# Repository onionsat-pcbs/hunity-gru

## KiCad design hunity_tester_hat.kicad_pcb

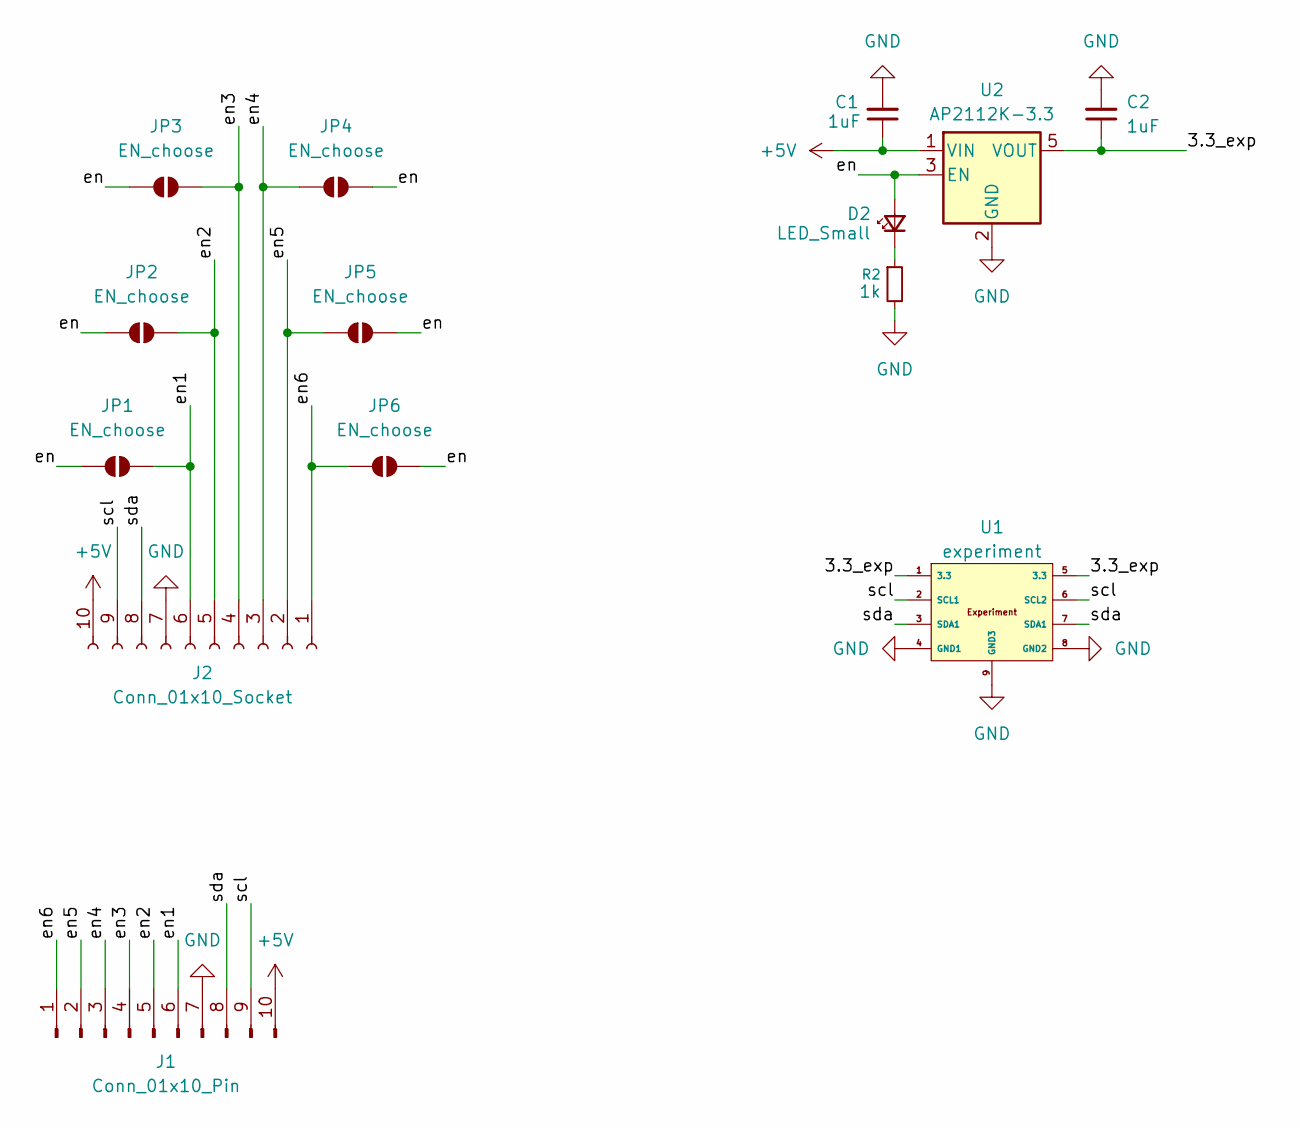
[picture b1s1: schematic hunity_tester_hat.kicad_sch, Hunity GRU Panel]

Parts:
C1, C2: 1uF; C_0603_1608Metric
D2: LED_Small; LED_0603_1608Metric
J1: Conn_01x10_Pin; PinHeader_1x10_P2.54mm_Horizontal
J2: Conn_01x10_Socket; PinSocket_1x10_P2.54mm_Horizontal
JP1, JP2, JP3, JP4, JP5, JP6: EN_choose; solder_jumper
R2: 1k; R_0603_1608Metric
U1: experiment; experiment_footprint
U2: AP2112K-3.3; SOT-23-5

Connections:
+5V: C1.1, J1.10, J2.10, U2.1 (VIN)
/3.3_exp: C2.1, U1.1 (3.3), U1.5 (3.3), U2.5 (VOUT)
/en: D2.2 (A), JP1.1 (A), JP2.1 (A), JP3.1 (A), JP4.2 (B), JP5.2 (B), JP6.2 (B), U2.3 (EN)
/en1: J1.6, J2.6, JP1.2 (B)
/en2: J1.5, J2.5, JP2.2 (B)
/en3: J1.4, J2.4, JP3.2 (B)
/en4: J1.3, J2.3, JP4.1 (A)
/en5: J1.2, J2.2, JP5.1 (A)
/en6: J1.1, J2.1, JP6.1 (A)
/scl: J1.9, J2.9, U1.2 (SCL1), U1.6 (SCL2)
/sda: J1.8, J2.8, U1.3 (SDA1), U1.7 (SDA1)
GND: C1.2, C2.2, J1.7, J2.7, R2.2, U1.4 (GND1), U1.8 (GND2), U1.9 (GND3), U2.2 (GND)
unnamed: D2.1 (K), R2.1

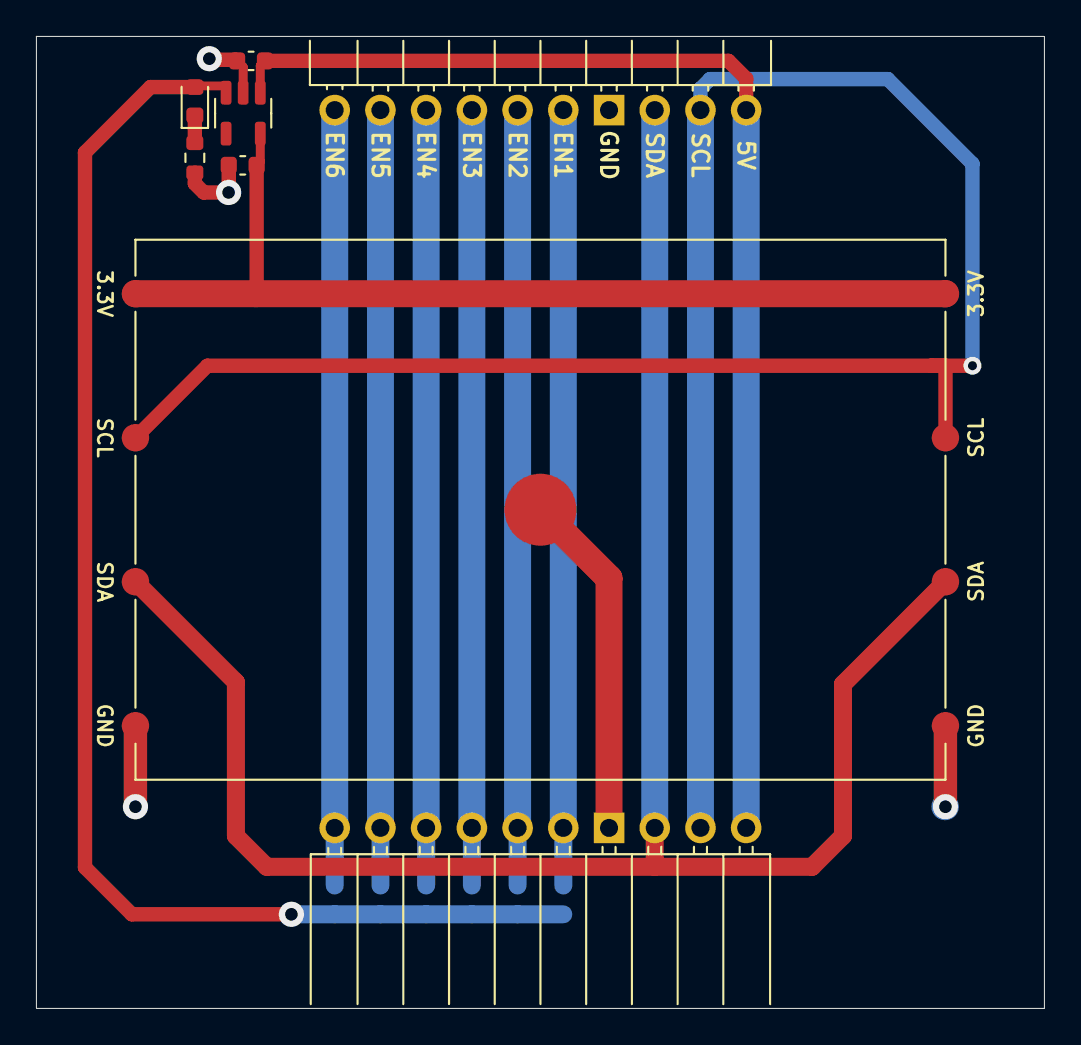
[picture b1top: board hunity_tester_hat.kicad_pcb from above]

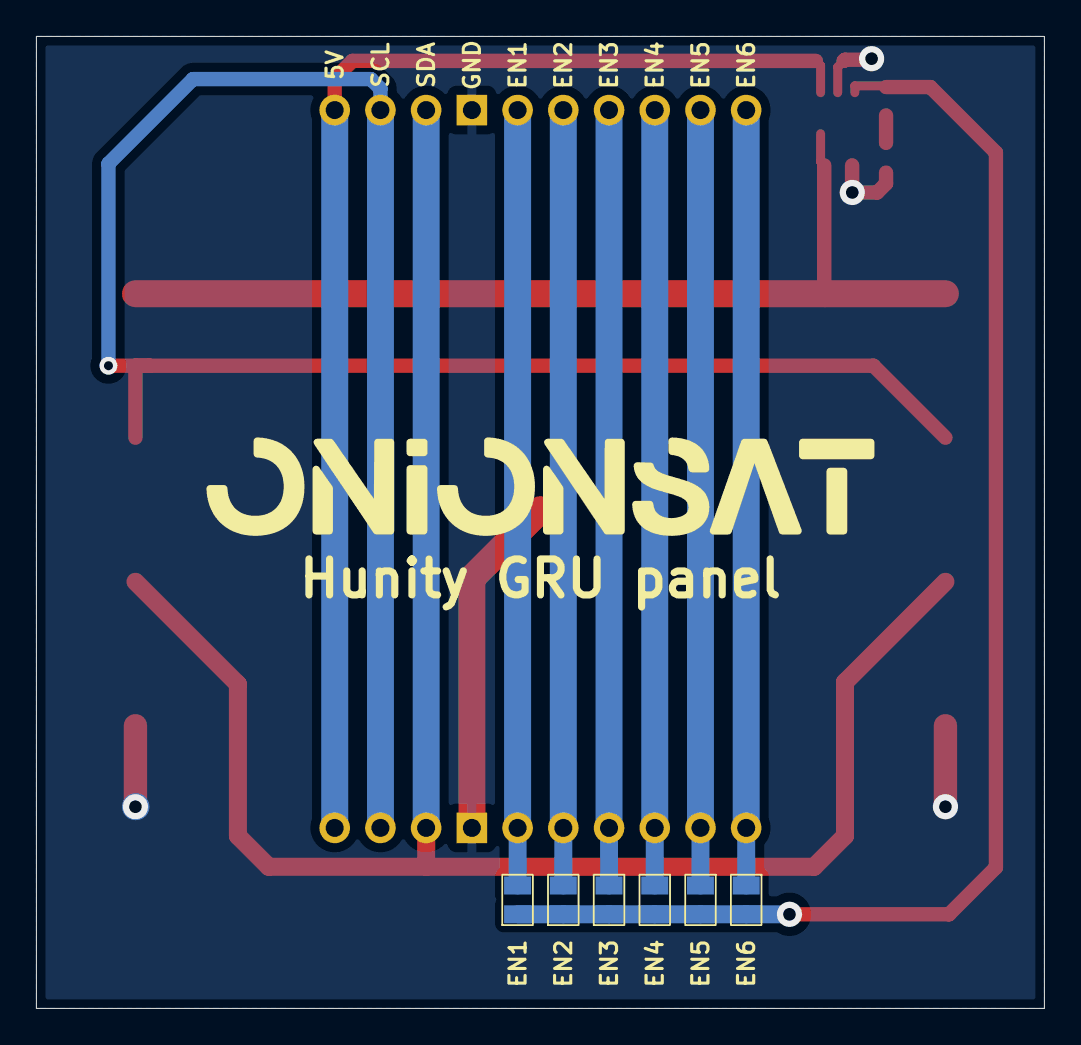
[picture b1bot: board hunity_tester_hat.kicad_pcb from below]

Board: 2 copper layers, 56.0 x 54.0 mm, 14 parts (6 on the bottom side), 13 nets.

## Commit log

2025-05-28 initial relase
2025-05-29 matrica nyákra (62x15mm)
2025-05-29 last fixes
2025-05-29 generating production files + labeling + DRC
2025-05-29 final labels+fixing production files
